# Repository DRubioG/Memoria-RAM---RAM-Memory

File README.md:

# Memoria RAM / RAM Memory
In this GitHub's repository will be placed the design of a Ram Memories

- [SODIMM](/SODIMM)

The SODIMM memories are the laptop memories

- [UDIMM](/UDIMM)

The UDIMM memories are the PC memories

Templates: 
https://github.com/DRubioG/KiCad_Templates

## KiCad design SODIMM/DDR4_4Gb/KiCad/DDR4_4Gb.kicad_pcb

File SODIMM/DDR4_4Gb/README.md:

# Folders

- [KiCad](/KiCad)

This folder contains the KiCad files for the RAM memory

- [Datasheet](/Datasheet)

This folder contains the datasheet files for the RAM memory

- [Schematic](DDR4_4Gb_SODIMM_Schematic.pdf)

The schematic of the RAM memory

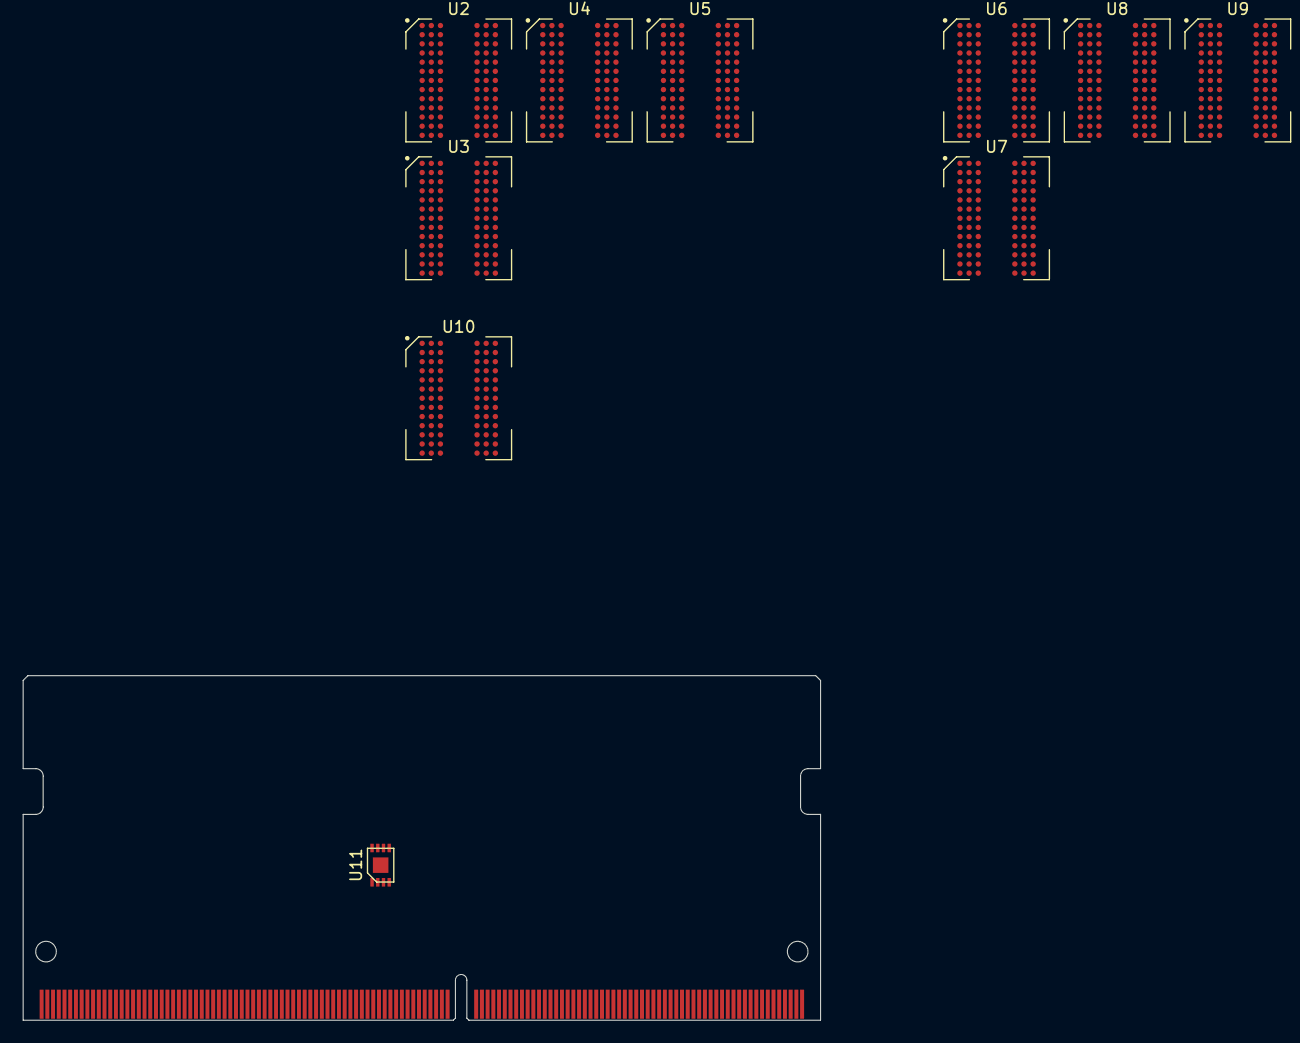
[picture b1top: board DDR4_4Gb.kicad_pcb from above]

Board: 2 copper layers, 69.7 x 30.1 mm, 11 parts (0 on the bottom side), 37 nets, no tracks yet.

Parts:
U1: DDR4_SODIMM
U2, U3, U4, U5, U6, U7, U8, U9, U10: MT40A512M8; BGA-117_9x13_9.0x10.5mm
U11: MCP9843; SOIC-8

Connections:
A0: U1.144, U2.L3, U3.L3, U4.L3, U5.L3, U6.L3, U7.L3, U8.L3, U9.L3, U10.L3
A1: U1.133, U2.L7, U3.L7, U4.L7, U5.L7, U6.L7, U7.L7, U8.L7, U9.L7, U10.L7
A2: U1.132, U2.M3, U3.M3, U4.M3, U5.M3, U6.M3, U7.M3, U8.M3, U9.M3, U10.M3
A3: U1.131, U2.K7, U3.K7, U4.K7, U5.K7, U6.K7, U7.K7, U8.K7, U9.K7, U10.K7
A4: U1.128, U2.K3, U3.K3, U4.K3, U5.K3, U6.K3, U7.K3, U8.K3, U9.K3, U10.K3
A5: U1.126, U2.L8, U3.L8, U4.L8, U5.L8, U6.L8, U7.L8, U8.L8, U9.L8, U10.L8
A6: U1.127, U2.L2, U3.L2, U4.L2, U5.L2, U6.L2, U7.L2, U8.L2, U9.L2, U10.L2
A7: U1.122, U2.M8, U3.M8, U4.M8, U5.M8, U6.M8, U7.M8, U8.M8, U9.M8, U10.M8
A8: U1.125, U2.M2, U3.M2, U4.M2, U5.M2, U6.M2, U7.M2, U8.M2, U9.M2, U10.M2
A9: U1.121, U2.M7, U3.M7, U4.M7, U5.M7, U6.M7, U7.M7, U8.M7, U9.M7, U10.M7
A10: U2.J3, U3.J3, U4.J3, U5.J3, U6.J3, U7.J3, U8.J3, U9.J3, U10.J3
A11: U1.120, U2.N2, U3.N2, U4.N2, U5.N2, U6.N2, U7.N2, U8.N2, U9.N2, U10.N2
A12: U2.J7, U3.J7, U4.J7, U5.J7, U6.J7, U7.J7, U8.J7, U9.J7, U10.J7
A13: U1.158, U2.N8, U3.N8, U4.N8, U5.N8, U6.N8, U7.N8, U8.N8, U9.N8, U10.N8
ACT_n: U1.114, U2.H3, U3.H3, U4.H3, U5.H3, U6.H3, U7.H3, U8.H3, U9.H3, U10.H3
ALERT_n: U1.116, U2.L9, U3.L9, U4.L9, U5.L9, U6.L9, U7.L9, U8.L9, U9.L9, U10.L9
BA0: U1.150, U2.K2, U3.K2, U4.K2, U5.K2, U6.K2, U7.K2, U8.K2, U9.K2, U10.K2
BA1: U1.145, U2.K8, U3.K8, U4.K8, U5.K8, U6.K8, U7.K8, U8.K8, U9.K8, U10.K8
BG0: U1.113, U2.J2, U3.J2, U4.J2, U5.J2, U6.J2, U7.J2, U8.J2, U9.J2, U10.J2
BG1: U1.115, U2.J8, U3.J8, U4.J8, U5.J8, U6.J8, U7.J8, U8.J8, U9.J8, U10.J8
CAS-A15: U2.H7, U3.H7, U4.H7, U5.H7, U6.H7, U7.H7, U8.H7, U9.H7, U10.H7
CKE0: U1.109, U2.G3, U3.G3, U4.G3, U5.G3, U6.G3, U7.G3, U8.G3, U9.G3, U10.G3
CS0_n: U1.149, U2.G7, U3.G7, U4.G7, U5.G7, U6.G7, U7.G7, U8.G7, U9.G7, U10.G7
EVENT_n: U1.134, U11.7
ODT0: U1.155, U2.F3, U3.F3, U4.F3, U5.F3, U6.F3, U7.F3, U8.F3, U9.F3, U10.F3
PAR: U1.143, U2.N3, U3.N3, U4.N3, U5.N3, U6.N3, U7.N3, U8.N3, U9.N3, U10.N3
RAS_n-A16: U1.152, U2.H8, U3.H8, U4.H8, U5.H8, U6.H8, U7.H8, U8.H8, U9.H8, U10.H8
RESET_n: U1.108, U2.L1, U3.L1, U4.L1, U5.L1, U6.L1, U7.L1, U8.L1, U9.L1, U10.L1
SA0: U1.256, U11.1
SA1: U1.260, U11.2
SA2: U1.166, U11.3
SCL: U1.253, U11.6
SDA: U1.254, U11.5
VDD: U1.111, U1.112, U1.117, U1.118, U1.123, U1.124, U1.129, U1.130, U1.135, U1.136, U1.141, U1.142, U1.147, U1.148, U1.153, U1.154, U1.159, U1.160, U1.163, U1.164, U1.255, U2.A1, U2.C7, U2.F1, U2.F9, U2.H1, U2.J1, U2.J9, U2.M1, U2.N9, U3.A1, U3.C7, U3.F1, U3.F9, U3.H1, U3.J1, U3.J9, U3.M1, U3.N9, U4.A1, U4.C7, U4.F1, U4.F9, U4.H1, U4.J1, U4.J9, U4.M1, U4.N9, U5.A1, U5.C7, U5.F1, U5.F9, U5.H1, U5.J1, U5.J9, U5.M1, U5.N9, U6.A1, U6.C7, U6.F1, U6.F9, U6.H1, U6.J1, U6.J9, U6.M1, U6.N9, U7.A1, U7.C7, U7.F1, U7.F9, U7.H1, U7.J1, U7.J9, U7.M1, U7.N9, U8.A1, U8.C7, U8.F1, U8.F9, U8.H1, U8.J1, U8.J9, U8.M1, U8.N9, U9.A1, U9.C7, U9.F1, U9.F9, U9.H1, U9.J1, U9.J9, U9.M1, U9.N9, U10.A1, U10.C7, U10.F1, U10.F9, U10.H1, U10.J1, U10.J9, U10.M1, U10.N9
VPP: U1.257, U1.259, U2.B1, U2.M9, U3.B1, U3.M9, U4.B1, U4.M9, U5.B1, U5.M9, U6.B1, U6.M9, U7.B1, U7.M9, U8.B1, U8.M9, U9.B1, U9.M9, U10.B1, U10.M9
VSS: U1.1, U1.2, U1.5, U1.6, U1.9, U1.10, U1.14, U1.15, U1.18, U1.19, U1.22, U1.23, U1.26, U1.27, U1.30, U1.31, U1.35, U1.36, U1.39, U1.40, U1.43, U1.44, U1.47, U1.48, U1.51, U1.52, U1.56, U1.57, U1.60, U1.61, U1.64, U1.65, U1.68, U1.69, U1.72, U1.73, U1.77, U1.78, U1.81, U1.82, U1.85, U1.86, U1.89, U1.90, U1.93, U1.94, U1.98, U1.99, U1.102, U1.103, U1.106, U1.107, U1.167, U1.168, U1.171, U1.172, U1.175, U1.176, U1.180, U1.181, U1.184, U1.185, U1.188, U1.189, U1.192, U1.193, U1.196, U1.197, U1.201, U1.202, U1.205, U1.206, U1.209, U1.210, U1.213, U1.214, U1.217, U1.218, U1.222, U1.223, U1.226, U1.227, U1.230, U1.231, U1.234, U1.235, U1.238, U1.239, U1.243, U1.244, U1.247, U1.248, U1.251, U1.252, U2.A2, U2.A8, U2.A9, U2.B2, U2.B8, U2.C1, U2.C8, U2.C9, U2.D1, U2.D9, U2.E1, U2.E2, U2.E8, U2.E9, U2.G1, U2.G9, U2.H9, U2.K1, U2.K9, U2.N1, U3.A2, U3.A8, U3.A9, U3.B2, U3.B8, U3.C1, U3.C8, U3.C9, U3.D1, U3.D9, U3.E1, U3.E2, U3.E8, U3.E9, U3.G1, U3.G9, U3.H9, U3.K1, U3.K9, U3.N1, U4.A2, U4.A8, U4.A9, U4.B2, U4.B8, U4.C1, U4.C8, U4.C9, U4.D1, U4.D9, U4.E1, U4.E2, U4.E8, U4.E9, U4.G1, U4.G9, U4.H9, U4.K1, U4.K9, U4.N1, U5.A2, U5.A8, U5.A9, U5.B2, U5.B8, U5.C1, U5.C8, U5.C9, U5.D1, U5.D9, U5.E1, U5.E2, U5.E8, U5.E9, U5.G1, U5.G9, U5.H9, U5.K1, U5.K9, U5.N1, U6.A2, U6.A8, U6.A9, U6.B2, U6.B8, U6.C1, U6.C8, U6.C9, U6.D1, U6.D9, U6.E1, U6.E2, U6.E8, U6.E9, U6.G1, U6.G9, U6.H9, U6.K1, U6.K9, U6.N1, U7.A2, U7.A8, U7.A9, U7.B2, U7.B8, U7.C1, U7.C8, U7.C9, U7.D1, U7.D9, U7.E1, U7.E2, U7.E8, U7.E9, U7.G1, U7.G9, U7.H9, U7.K1, U7.K9, U7.N1, U8.A2, U8.A8, U8.A9, U8.B2, U8.B8, U8.C1, U8.C8, U8.C9, U8.D1, U8.D9, U8.E1, U8.E2, U8.E8, U8.E9, U8.G1, U8.G9, U8.H9, U8.K1, U8.K9, U8.N1, U9.A2, U9.A8, U9.A9, U9.B2, U9.B8, U9.C1, U9.C8, U9.C9, U9.D1, U9.D9, U9.E1, U9.E2, U9.E8, U9.E9, U9.G1, U9.G9, U9.H9, U9.K1, U9.K9, U9.N1, U10.A2, U10.A8, U10.A9, U10.B2, U10.B8, U10.C1, U10.C8, U10.C9, U10.D1, U10.D9, U10.E1, U10.E2, U10.E8, U10.E9, U10.G1, U10.G9, U10.H9, U10.K1, U10.K9, U10.N1, U11.9
WE_n-A14: U1.151, U2.H2, U3.H2, U4.H2, U5.H2, U6.H2, U7.H2, U8.H2, U9.H2, U10.H2
